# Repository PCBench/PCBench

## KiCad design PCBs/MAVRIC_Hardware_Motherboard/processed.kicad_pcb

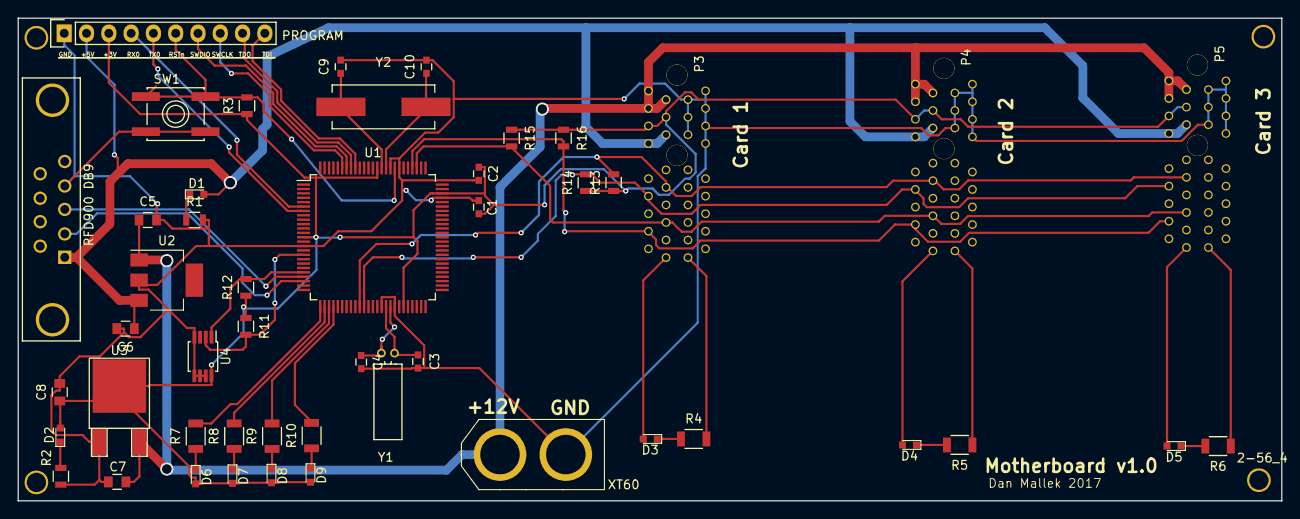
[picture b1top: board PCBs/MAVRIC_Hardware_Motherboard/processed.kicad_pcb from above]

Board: 2 copper layers, 144.0 x 55.0 mm, 52 parts (0 on the bottom side), 42 nets.

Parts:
2-56, 2-56_2, 2-56_3, 2-56_4: 2-56 Standoff; 2-56_Standoff
C1: 4.7u; C_0603
C2: 100n; C_0603
C3, C4: 22p; C_0603
C5, C7: 10u; C_0805
C6, C8: 22u; C_0805
C9, C10: 20p; C_0603
D1: RFD900 PWR LED; LED_0603
D2, D3, D4, D5, D6, D7, D8, D9: LED; LED_0603
P3: PCIe Card 1; PCIe_36
P4: PCIe Card 2; PCIe_36
P5: PCIe Card 3; PCIe_36
PROGRAM: PROGRAM+DEBUG; Pin_Header_Straight_1x10
R1, R2, R3: 10k; R_0805
R4, R5, R6, R7, R8, R9, R10: 220; R_1206
R11, R12, R13, R14, R15, R16: 2.2k; R_0805
RFD900 DB9: DB9; DB9FD
SW1: SPST; SW_SPST_EVQP0
U1: MSP432; LQFP-100_14x14mm_Pitch0.5mm
U2: LM340MP-5.0; SOT-223
U3: LD1086DT33TR; TO-252-2Lead
U4: MCP9808; MSOP-8_3x3mm_Pitch0.65mm
XT60: 12v POWER; XT60
Y1: 32.768khz; Crystal_Round_Horizontal_3mm
Y2: 48MHz; Crystal_HC49-SD_SMD

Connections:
+3V3: C1.1, C2.1, C8.1, D2.2, D6.2, D7.2, D8.2, D9.2, P3.7, P3.9, P4.7, P4.9, P5.7, P5.9, PROGRAM.3, R3.1, R11.1, R12.1, R13.1, R14.1, R15.1, R16.1, U1.13, U1.45, U1.73, U1.87, U3.2, U4.8
+5V: C6.1, D1.2, P3.11, P3.13, P4.11, P4.13, P5.11, P5.13, PROGRAM.2, RFD900 DB9.1, U2.3
+12V: C5.1, C7.1, P3.1, P3.3, P3.5, P4.1, P4.3, P4.5, P5.1, P5.3, P5.5, U2.1, U3.3, XT60.1
/HFXIN: C9.1, U1.86, Y2.1
/HFXOUT: C10.1, U1.85, Y2.2
/LFXIN: C3.1, U1.41, Y1.1
/LFXOUT: C4.1, U1.42, Y1.2
/RSTn: PROGRAM.6, R3.2, SW1.1, U1.83
/RX1: RFD900 DB9.2, U1.23
/SCL0: P3.21, P4.21, P5.21, R14.2, U1.36
/SCL1: P3.29, P4.29, P5.29, R16.2, U1.79
/SCL2: R11.2, U1.17, U4.2
/SDA0: P3.19, P4.19, P5.19, R13.2, U1.35
/SDA1: P3.27, P4.27, P5.27, R15.2, U1.78
/SDA2: R12.2, U1.21, U4.1
/SWCLK: PROGRAM.8, U1.95
/SWDIO: PROGRAM.7, U1.94
/TDI: PROGRAM.10, U1.92
/TDO_SWO: PROGRAM.9, U1.93
/TX1: RFD900 DB9.3, U1.22
/TestLED1: R7.2, U1.26
/TestLED2: R8.2, U1.27
/TestLED3: R9.2, U1.28
/TestLED4: R10.2, U1.29
/UCA0RXD: PROGRAM.4, U1.6
/UCA0TXD: PROGRAM.5, U1.7
GND: C1.2, C2.2, C3.2, C4.2, C5.2, C6.2, C7.2, C8.2, C9.2, C10.2, P3.2, P3.4, P3.6, P3.8, P3.10, P3.12, P3.14, P4.2, P4.4, P4.6, P4.8, P4.10, P4.12, P4.14, P5.2, P5.4, P5.6, P5.8, P5.10, P5.12, P5.14, PROGRAM.1, R1.2, R2.1, RFD900 DB9.4, SW1.2, U1.15, U1.40, U1.43, U1.72, U1.82, U1.84, U2.2, U3.1, U4.4, U4.5, U4.6, U4.7, XT60.2
unnamed: D1.1, R1.1
unnamed: D2.1, R2.2
unnamed: D3.1, R4.1
unnamed: D3.2, P3.35
unnamed: D4.1, R5.2
unnamed: D4.2, P4.35
unnamed: D5.1, R6.2
unnamed: D5.2, P5.35
unnamed: D6.1, R7.1
unnamed: D7.1, R8.1
unnamed: D8.1, R9.1
unnamed: D9.1, R10.1
unnamed: P3.36, R4.2
unnamed: P4.36, R5.1
unnamed: P5.36, R6.1

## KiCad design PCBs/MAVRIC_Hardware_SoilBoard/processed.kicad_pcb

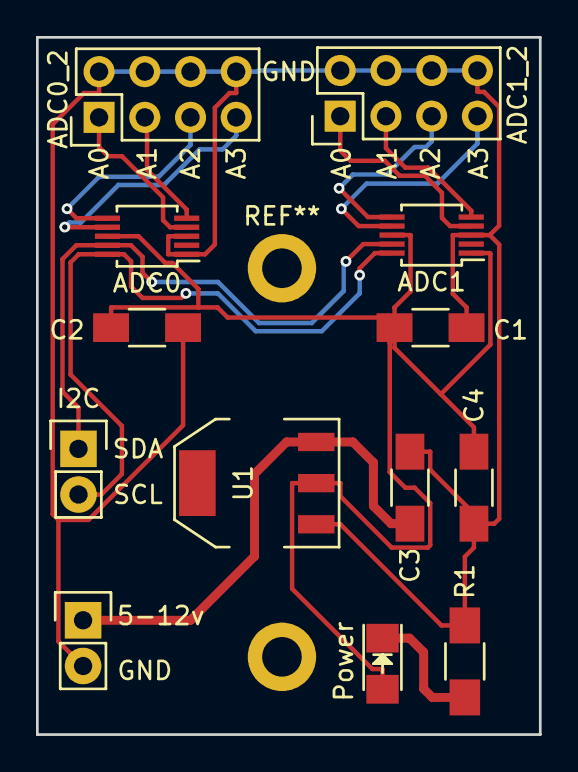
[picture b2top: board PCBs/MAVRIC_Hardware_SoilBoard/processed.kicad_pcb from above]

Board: 2 copper layers, 27.9 x 38.7 mm, 14 parts (1 on the bottom side), 14 nets.

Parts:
5-12v: Power; Pin_Header_Straight_1x02
ADC0, ADC1: ADS1015; MSOP-10_3x3mm_Pitch0.5mm
ADC0_2: ADC0; Pin_Header_Straight_2x04
ADC1_2: ADC1; Pin_Header_Straight_2x04
C1, C2, C3: 100n; C_1206_HandSoldering
C4: 10u; C_1206_HandSoldering
I2C: I2C; Pin_Header_Straight_1x02
MAV3: MAVRIC
Power: Power; LED_1206
R1: 220; R_1206_HandSoldering
U1: LD1117S33TR; SOT-223

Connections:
+3V3: ADC0.8, ADC1.1, ADC1.8, C1.1, C2.1, C4.1, Power.2, U1.2
+12V: 5-12v.1, C3.1, U1.3
/A00: ADC0.4, ADC0_2.1
/A01: ADC0.5, ADC0_2.3
/A02: ADC0.6, ADC0_2.5
/A03: ADC0.7, ADC0_2.7
/A10: ADC1.4, ADC1_2.1
/A11: ADC1.5, ADC1_2.3
/A12: ADC1.6, ADC1_2.5
/A13: ADC1.7, ADC1_2.7
/SCL: ADC0.10, ADC1.10, I2C.2
/SDA: ADC0.9, ADC1.9, I2C.1
GND: 5-12v.2, ADC0.1, ADC0.3, ADC0_2.2, ADC0_2.4, ADC0_2.6, ADC0_2.8, ADC1.3, ADC1_2.2, ADC1_2.4, ADC1_2.6, ADC1_2.8, C1.2, C2.2, C3.2, C4.2, R1.2, U1.1
unnamed: Power.1, R1.1

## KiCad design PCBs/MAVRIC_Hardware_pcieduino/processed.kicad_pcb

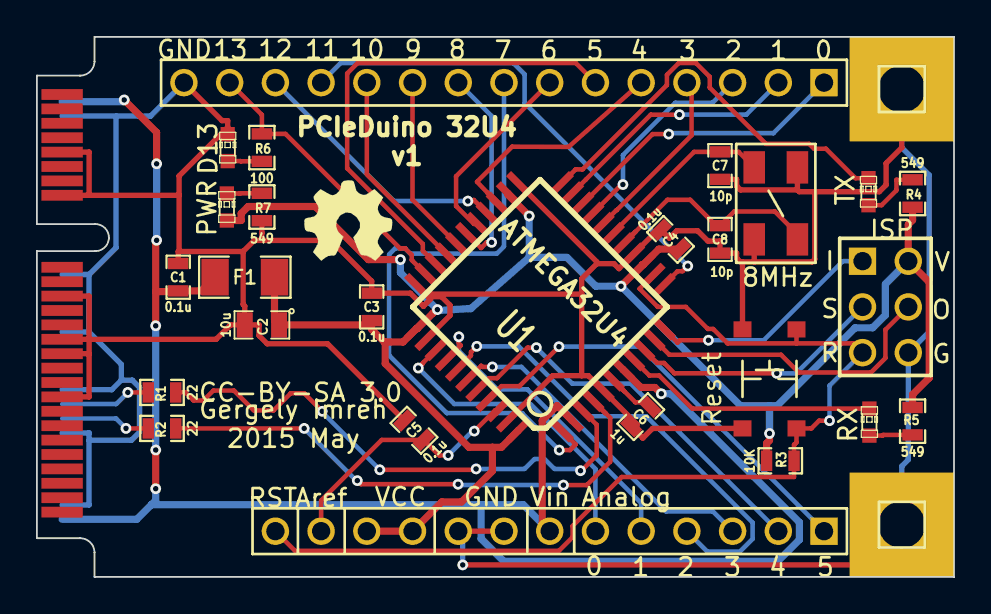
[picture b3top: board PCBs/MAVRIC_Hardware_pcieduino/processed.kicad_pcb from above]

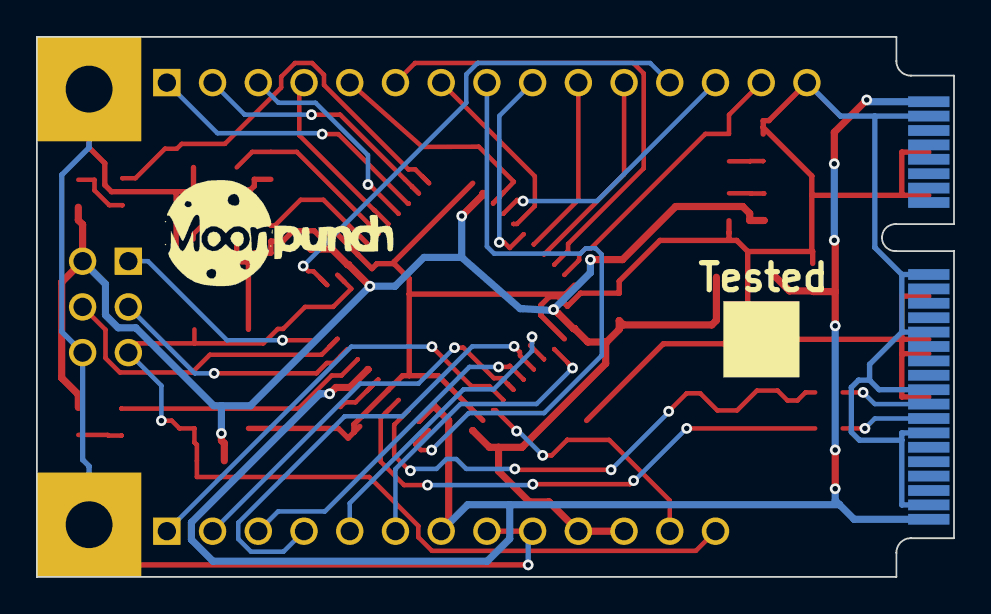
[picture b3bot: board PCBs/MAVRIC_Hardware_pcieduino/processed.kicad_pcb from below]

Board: 2 copper layers, 51.0 x 30.0 mm, 32 parts (2 on the bottom side), 41 nets.

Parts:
C1, C3, C4, C5: 0.1u; SM0603_Capa
C2: 10u; SM0805
C6: 1u; SM0603_Capa
C7, C8: 10p; SM0603_Capa
D1: TX; LED-0603
D2: RX; LED-0603
D3: D13; LED-0603
D4: PWR; LED-0603
F1: FUSE; SM1206
J1: PCIE-MINI; miniPCIeConn
J2: ISP; pin_array_3x2
J3: DIGITAL; PIN_ARRAY_15x1
J4: ANALOG_POWER; PIN_ARRAY_13x1
MOONPUNCH: LOGO
MOUNTING_HOLE1, MOUNTING_HOLE2: CONN_1; PIN_ARRAY_1
OSHW: LOGO; OSHW
R1, R2: 22; SM0603_Resistor
R3: 10K; SM0603_Resistor
R4, R5, R7: 549; SM0603_Resistor
R6: 100; SM0603_Resistor
SW1: Reset; SMD_SWITCH
TESTED: LOGO; SQUARE
U1: ATMEGA32U4; TQFP44
X1: 8MHz; SMDXTAL_50x32

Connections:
/A0: J4.6, U1.36
/A1: J4.5, U1.37
/A2: J4.4, U1.38
/A3: J4.3, U1.39
/A4: J4.2, U1.40
/A5: J4.1, U1.41
/AREF: C5.1, J4.12, U1.42
/D0/RXI: J3.1, U1.20
/D1/TXO: J3.2, U1.21
/D2/SDA: J3.3, U1.19
/D3/SCL: J3.4, U1.18
/D4: J3.5, U1.25
/D5: J3.6, U1.31
/D6: J3.7, U1.27
/D7: J3.8, U1.1
/D8: J3.9, U1.28
/D9: J3.10, U1.29
/D10: J3.11, U1.30
/D11: J3.12, U1.12
/D12: J3.13, U1.26
/D13: J3.14, R6.1, U1.32
/D+: R2.1, U1.4
/D-: R1.1, U1.3
/MISO: J2.1, U1.11
/MOSI: J2.4, U1.10
/RESET: J2.5, J4.13, R3.2, SW1.2, U1.13
/RXLED: D2.2, U1.8
/SCK: J2.3, U1.9
/TXLED: D1.2, U1.22
/UVCC: C1.1, F1.1, J1.2, J1.52, J4.7, U1.2, U1.7
GND: C1.2, C2.2, C3.2, C4.2, C5.2, C6.2, C7.2, C8.2, D3.2, J1.4, J1.9, J1.15, J1.18, J1.21, J1.26, J1.27, J1.29, J1.34, J1.35, J1.40, J1.50, J2.6, J3.15, J4.8, J4.9, MOUNTING_HOLE1.1, MOUNTING_HOLE2.1, R7.2, SW1.1, U1.5, U1.15, U1.23, U1.33, U1.35, U1.43, X1.3
unnamed: J1.36, R1.2
unnamed: J1.38, R2.2
unnamed: C6.1, U1.6
unnamed: D4.2, R7.1
unnamed: C8.1, U1.16, X1.2
unnamed: C7.1, U1.17, X1.1
unnamed: D3.1, R6.2
unnamed: D1.1, R4.1
unnamed: D2.1, R5.1
VCC: C2.1, C3.1, C4.1, D4.1, F1.2, J2.2, J4.10, J4.11, R3.1, R4.2, R5.2, U1.14, U1.24, U1.34, U1.44

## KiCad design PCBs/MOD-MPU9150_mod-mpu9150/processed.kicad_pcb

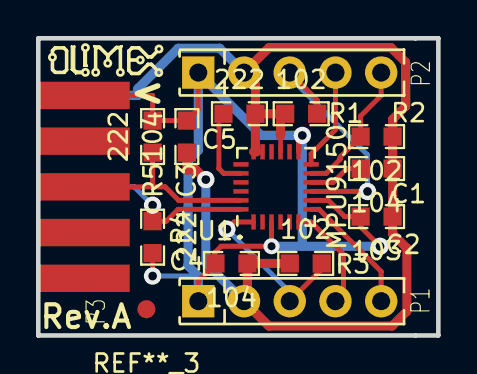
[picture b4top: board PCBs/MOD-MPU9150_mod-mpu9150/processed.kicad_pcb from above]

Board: 2 copper layers, 22.2 x 16.5 mm, 14 parts (0 on the bottom side), 12 nets.

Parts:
C1, C3, C4: 104; C_0603
C2: 103; C_0603
C5: 222; C_0603
P1, P2: CONN_01X05; SIP5_Housing
P3: HE10-10; UEXTF
R1, R2, R3: 102; R_0603
R4, R5: 222; R_0603
U1: MPU9150; QFN-24-1EP_4x4mm_Pitch0.5mm

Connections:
/SCL: P3.5, R5.2, U1.23
/SDA: P3.6, R4.2, U1.24
AD0: P2.3, R1.1, U1.9
CLKIN: P1.3, R3.1, U1.1
GND: C1.2, C2.2, C3.2, C4.2, C5.1, P1.2, P2.2, P3.2, R1.2, R2.2, R3.2, U1.15, U1.17, U1.18
unnamed: C1.1, U1.10
unnamed: C5.2, U1.20
unnamed: P1.4, U1.6
unnamed: P1.5, U1.7
unnamed: P2.4, U1.12
unnamed: P2.5, R2.1, U1.11
VDD: C2.1, C3.1, C4.1, P1.1, P2.1, P3.1, R4.1, R5.1, U1.3, U1.8, U1.13

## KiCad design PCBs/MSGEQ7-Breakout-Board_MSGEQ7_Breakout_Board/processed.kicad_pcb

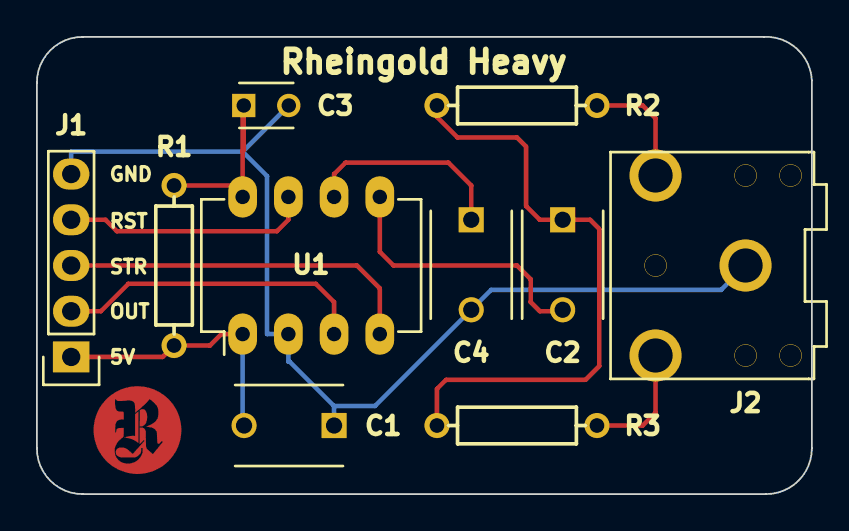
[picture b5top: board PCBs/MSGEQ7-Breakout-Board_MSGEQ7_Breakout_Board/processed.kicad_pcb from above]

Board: 2 copper layers, 43.1 x 25.4 mm, 13 parts (0 on the bottom side), 11 nets.

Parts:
C1, C2, C4: 0.1uF; C_Disc_D6_P5
C3: 33pF; C_Disc_D3_P2.5
J1: BREAKOUT_BOARD_HEADER; Pin_Header_Straight_1x05
J2: STEREO_MINI_JACK; 3.5mm_Stereo_Jack_SJ1-3523NG
R1: 200K; PTH_Resistor
R2, R3: 22K; PTH_Resistor
U1: MSGEQ7; DIP-8_W7.62mm_LongPads
VAL: REF; Logo_RH_Circle_R_B.SilkS_.750in_flipped
VAL_2: REF; Logo_RH_Circle_R__F.Mask_.2in
VAL_3: REF; Logo_RH_Circle_R__F.Cu_.2in

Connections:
+5V: C1.2, J1.1, R1.2, U1.1
GND: C1.1, C3.2, C4.2, J1.5, J2.1, U1.2
unnamed: C2.1, R2.1, R3.1
unnamed: C2.2, U1.5
unnamed: C3.1, R1.1, U1.8
unnamed: C4.1, U1.6
unnamed: J2.2, R2.2
unnamed: J2.3, R3.2
OUT: J1.2, U1.3
RESET_IN: J1.4, U1.7
STROBE: J1.3, U1.4

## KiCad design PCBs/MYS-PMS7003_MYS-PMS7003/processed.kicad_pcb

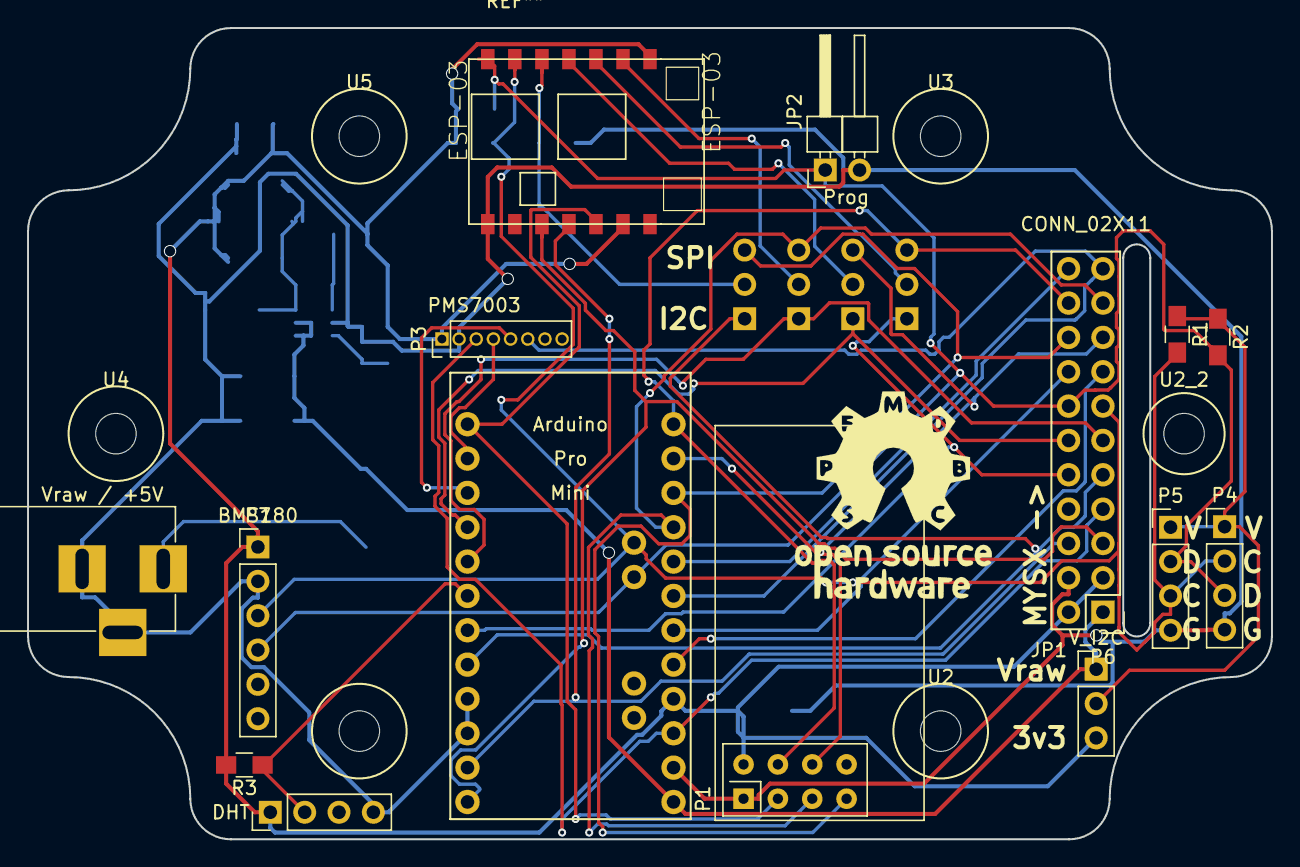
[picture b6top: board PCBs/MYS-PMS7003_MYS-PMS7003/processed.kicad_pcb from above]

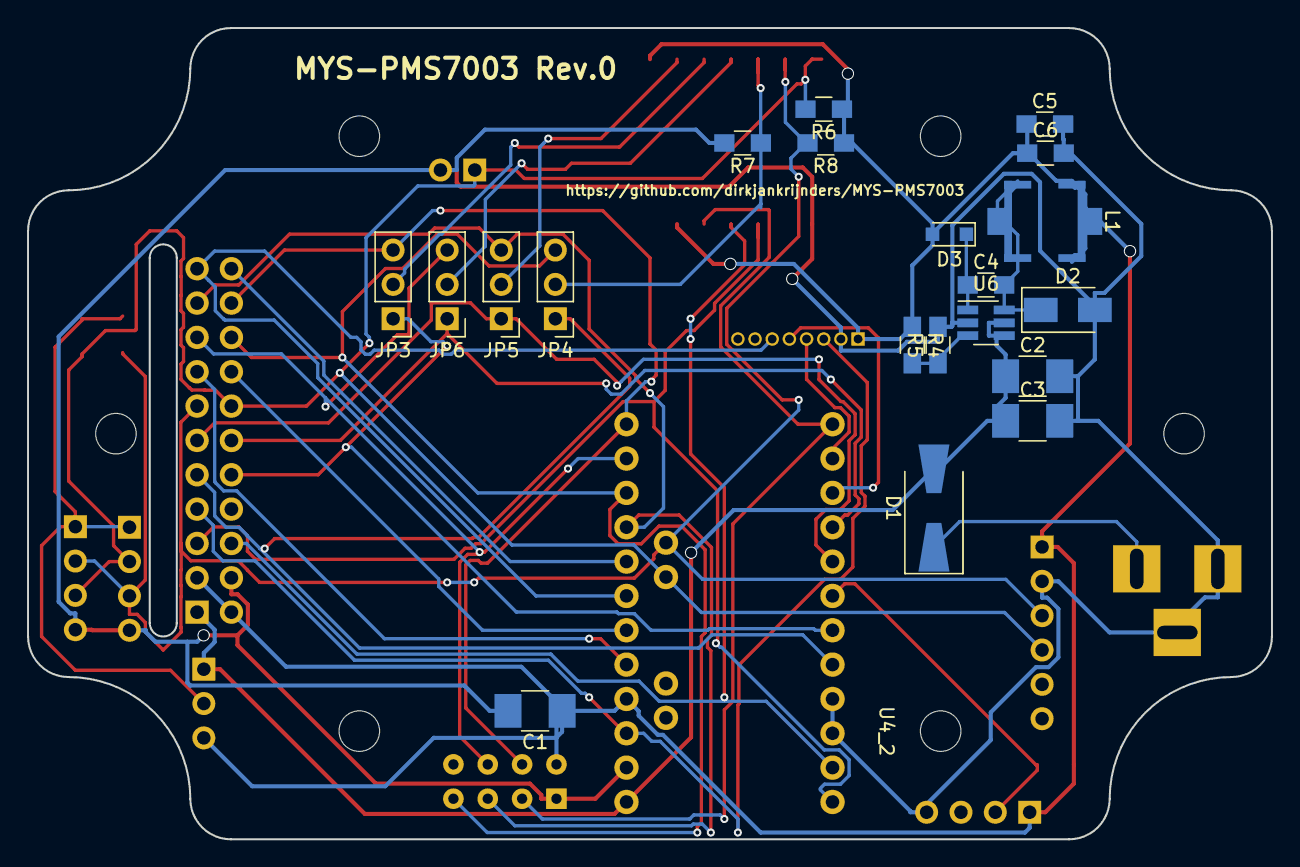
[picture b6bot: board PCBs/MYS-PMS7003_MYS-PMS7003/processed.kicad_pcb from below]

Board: 2 copper layers, 92.0 x 60.0 mm, 41 parts (21 on the bottom side), 33 nets.

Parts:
C1, C2, C3: 4u7; R_1210_HandSoldering
C4: 100 nF; R_0805_HandSoldering
C5, C6: 10u; R_0805_HandSoldering
D1: DIODE; D_SMA-SMB_Universal_Handsoldering
D2: B140; D_SMA
D3: 1N4148; D_SOD-323_HandSoldering
ESP-03: ESP-03
JP1, JP3, JP4, JP5, JP6: Jumper_NC_Dual; Pin_Header_Straight_1x03_Pitch2.54mm
JP2: Jumper; Pin_Header_Angled_1x02_Pitch2.54mm
L1: 15 μH; L_Coilcraft_MSS6132
P1: CONN_02X04; nRF24L01_Breakout
P2: CONN_01X03; Pin_Header_Straight_1x04_Pitch2.54mm
P3: CONN_01X08; Pin_Header_Straight_1x08_Pitch1.27mm
P4, P5: CONN_01X04; Pin_Header_Straight_1x04_Pitch2.54mm
P6: CONN_02X11; MYSX_2.6
P7: CONN_01X06; Pin_Header_Straight_1x06_Pitch2.54mm
R1, R2, R3: R; R_0805_HandSoldering
R4: 31k6; R_0805_HandSoldering
R5: 10k; R_0805_HandSoldering
R6, R7, R8: 12k; R_0805_HandSoldering
U1: Arduino_Pro_Micro; Arduino_Pro_Mini
U2, U2_2, U3, U4, U4_2, U5: M3_Mounting_hole; MountingHole_3mm
U6: MCP16301; SOT-23-6_Handsoldering
Vraw / +5V: BARREL_JACK

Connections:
+3V3: C1.1, C5.1, C6.1, D3.2, ESP-03.6, ESP-03.8, JP1.3, L1.2, P1.2, P2.1, P3.1, P6.2, P6.3, P7.1, R3.2, R4.1, R6.1, R8.1, U1.16
/DHT_DATA: P2.2, R3.1, U1.6
/MYSX_D1_DFM: ESP-03.3, P6.5, U1.12
/MYSX_D2_DTM: ESP-03.4, P6.6, U1.11
/MYSX_D3_INT: JP4.1, P6.9, U1.8
/MYSX_D4_INT: JP3.1, P6.10, U1.7
/MYSX_D5_PWM: JP5.1, P6.11, U1.5
/MYSX_D6_PWM: JP6.1, P6.12, U1.4
/MYSX_D7_SCL: ESP-03.13, P4.2, P5.3, P6.13, P7.3, R1.2, R8.2, U1.26
/MYSX_D8_SDA: ESP-03.14, JP2.1, P4.3, P5.2, P6.14, P7.4, R2.2, R6.2, U1.25
/MYSX_D9_A3: P6.15, U1.17
/MYSX_D10_A4: P6.16, U1.18
/MYSX_D11_MOSI: JP6.3, P1.6, P6.17, U1.23
/MYSX_D12_MISO: JP4.3, P1.7, P6.18, U1.22
/MYSX_D13_SCLK: JP5.3, P1.5, P6.19, U1.21
/MYSX_D14_CS: JP3.3, P1.4, P6.20, U1.24
/MYSX_D15_A5: P3.6, P6.21, U1.19
/MYSX_D16_A6: P6.22, U1.20
/MYSX_RST: P3.3, P6.7, U1.15
/NRF24_CE: ESP-03.5, P1.3, U1.1
/SS_RX: P3.4, U1.2
/SS_TX: P3.5, U1.3
/Vraw: C2.1, C3.1, D1.2, JP1.1, P6.1, U1.13, U6.4, U6.5
GND: C1.2, C2.2, C3.2, C5.2, C6.2, D2.2, ESP-03.1, JP2.2, P1.1, P2.4, P3.2, P4.4, P5.4, P6.4, P7.2, R5.2, R7.2, U1.9, U1.10, U1.14, U6.2, Vraw / +5V.2, Vraw / +5V.3
unnamed: C4.1, D3.1, U6.1
unnamed: C4.2, D2.1, L1.1, U6.6
unnamed: D1.1, Vraw / +5V.1
unnamed: JP1.2, P4.1, P5.1, R1.1, R2.1
unnamed: ESP-03.10, JP3.2
unnamed: ESP-03.12, JP4.2, R7.1
unnamed: ESP-03.9, JP5.2
unnamed: ESP-03.11, JP6.2
unnamed: R4.2, R5.1, U6.3

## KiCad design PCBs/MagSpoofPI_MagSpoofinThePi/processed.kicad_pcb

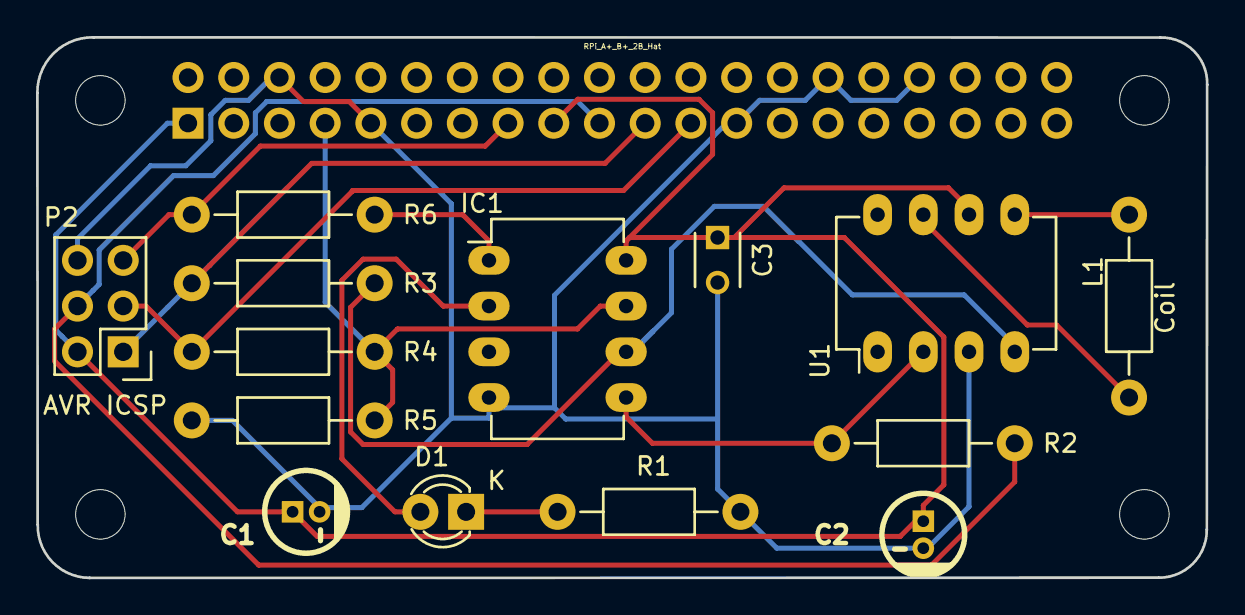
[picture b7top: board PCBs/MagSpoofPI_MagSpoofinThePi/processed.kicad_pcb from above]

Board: 2 copper layers, 65.0 x 30.0 mm, 16 parts (1 on the bottom side), 14 nets.

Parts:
C1, C2: 100uF; CP_4x5mm
C3: 0.1uF; C_Disc_D3_P2.5
D1: LED; LED-3MM
IC1: ATTINY85-P; DIP-8_W7.62mm_LongPads
L1: Coil; Resistor_Horizontal_RM10mm
Noname_1: OSHW-Logo; Symbol_OSHW-Logo_SilkScreen
P2: AVR ICSP; Pin_Header_Straight_2x03
R1: 330; Resistor_Horizontal_RM10mm
R2, R3, R4, R6: 1K; Resistor_Horizontal_RM10mm
R5: 10K; Resistor_Horizontal_RM10mm
U1: TC4424; DIP-8_W7.62mm_LongPads
U2: RPi_A+_B+_2B_Hat; z_RPiZero_Hat_NPTH

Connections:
/GPIO4: IC1.7, R4.2, R5.1, U2.7
/MISO: P2.1, R3.1, U2.21
/MOSI: P2.4, R2.1, U2.19
/RST: P2.5, R6.2, U2.15
/SCK: P2.3, R4.1, U2.23
GND: C1.2, C2.2, C3.2, IC1.4, P2.6, R1.2, R5.2, U1.3, U2.6, U2.9, U2.25, U2.30, U2.34
unnamed: D1.1, R1.1
unnamed: D1.2, IC1.2
unnamed: IC1.1, R6.1
unnamed: IC1.5, R2.2, U1.2
unnamed: IC1.6, R3.2, U1.4
unnamed: L1.1, U1.7
unnamed: L1.2, U1.5
VCC: C1.1, C2.1, C3.1, IC1.8, P2.2, U1.6, U2.1, U2.17

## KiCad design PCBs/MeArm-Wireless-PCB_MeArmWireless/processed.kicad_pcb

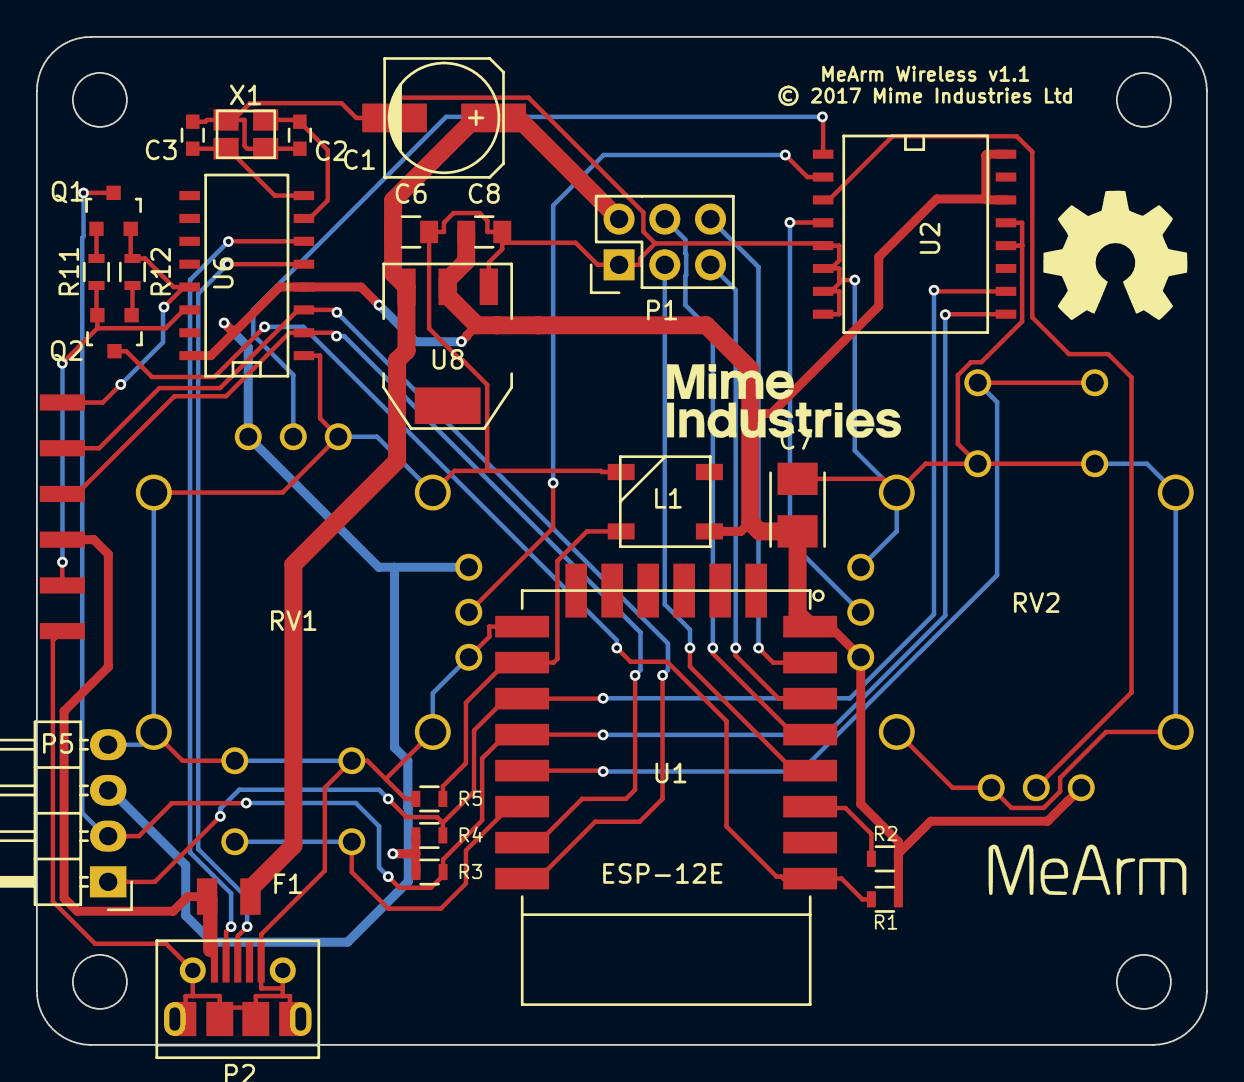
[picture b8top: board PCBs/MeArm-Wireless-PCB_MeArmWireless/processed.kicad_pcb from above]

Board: 2 copper layers, 65.0 x 56.0 mm, 31 parts (0 on the bottom side), 29 nets.

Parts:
ART1: OSHW-LOGO; OSHW_LOGO
ART2: LOGO; MEARM_LOGO_NEW
ART3: LOGO; MIME_LOGO
C1: 470uF; c_elec_6.3x7.7
C2, C3: 22pF; C_0603
C6, C8: 10uF; C_0805
C7: 100uF; TantalC_SizeB_EIA-3528_Reflow
F1: 1A; Fuse_SMD1206_Reflow
L1: WS2812B
P1: CONN_02X03; Pin_Header_Straight_2x03
P2: USB_OTG; MOLEX_MICRO_USB
P4: CONN_01X06; 6-PIN-EDGE-CONN
P5: CONN_01X04; Pin_Header_Angled_1x04
Q1, Q2: S8050; SOT-23
R1, R2, R3, R4, R5, R11, R12: 10k; R_0603
RV1, RV2: DUAL_POT_JOYSTICK; JOYSTICK
U1: ESP-12E
U2: PCF8591; SO-16-W
U6: CH340G; SO-16-N
U8: LD1117S33CTR; SOT-223
X1: 12MHz; crystal_FA238-TSX3225

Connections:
+3V3: C7.1, C8.1, L1.1, P5.3, R1.1, R2.1, R3.1, R4.1, RV1.1, RV1.4, RV2.1, RV2.4, U1.8, U2.14, U2.16, U6.4, U6.16, U8.2
+5V: F1.1, P2.1, P4.3
BASE_SERVO: P1.3, U1.4
BUTTON1: RV1.8, U1.20
BUTTON2: RV2.8, U1.19
GND: C1.2, C2.2, C3.2, C6.2, C7.2, C8.2, L1.3, P1.1, P2.5, P2.6, P4.1, P5.4, R5.2, RV1.3, RV1.6, RV1.7, RV1.9, RV2.3, RV2.6, RV2.7, RV2.9, U1.15, U2.5, U2.6, U2.7, U2.8, U2.12, U2.13, U6.1, U8.1, X1.3
GRIP_SERVO: P1.6, U1.7
LED: L1.4, R5.1, U1.16
LEFT_SERVO: P1.4, U1.5
unnamed: C2.1, U6.7, X1.1
unnamed: C3.1, U6.8, X1.2
unnamed: P2.2, U6.6
unnamed: P2.3, U6.5
unnamed: P4.2, Q2.1, R11.1, U6.14
unnamed: P4.6, Q1.1, R12.1, U6.13
unnamed: Q1.2, R11.2
unnamed: Q2.2, R12.2
unnamed: R2.2, U1.3
unnamed: RV1.2, U2.1
unnamed: RV1.5, U2.2
unnamed: RV2.2, U2.3
unnamed: RV2.5, U2.4
RESET: Q2.3, R1.2, U1.1
RIGHT_SERVO: P1.5, U1.6
RX: P4.4, U1.21, U6.2
SCL: P5.1, R4.2, U1.17, U2.10
SDA: P5.2, Q1.3, R3.2, U1.18, U2.9
TX: P4.5, U1.22, U6.3
VSS: C1.1, C6.1, F1.2, P1.2, U8.3

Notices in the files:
PCBs/MAVRIC_Hardware_pcieduino/processed.kicad_pcb:
CC-BY-SA 3.0
PCBs/MeArm-Wireless-PCB_MeArmWireless/processed.kicad_pcb:
© 2017 Mime Industries Ltd
